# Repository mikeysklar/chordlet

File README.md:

# chordlet
Add a keyboard to your controller.

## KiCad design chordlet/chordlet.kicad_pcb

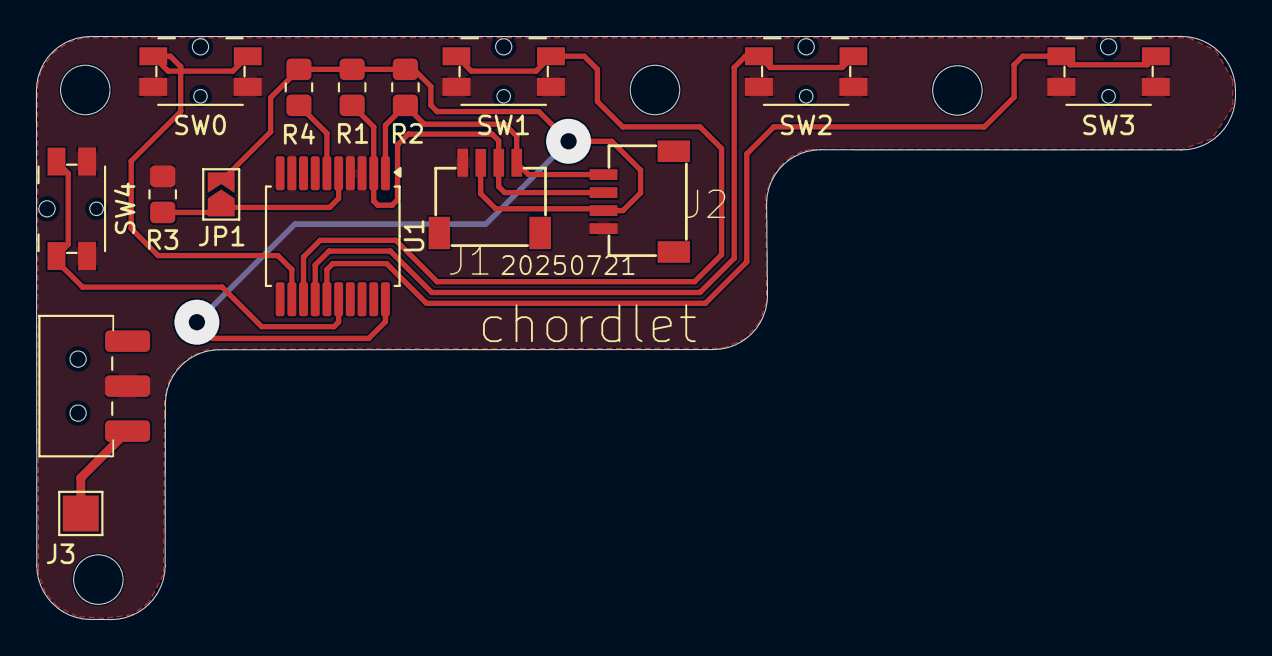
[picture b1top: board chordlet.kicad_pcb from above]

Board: 2 copper layers, 66.6 x 32.4 mm, 15 parts (0 on the bottom side), 12 nets.

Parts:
J1, J2: Conn_01x06_Socket; JST_SH4
J3: Conn_01x01_Pin; TestPoint_Pad_2.0x2.0mm
JP1: SolderJumper_2_Open; SolderJumper-2_P1.3mm_Open_TrianglePad1.0x1.5mm
R1, R2, R3, R4: 10k; R_0805_2012Metric_Pad1.20x1.40mm_HandSolder
SW0, SW1, SW2, SW3, SW4: SW_Push; Panasonic_EVQPUL_EVQPUC
SW5: SW_DPDT_x2; Untitled
U1: MCP23008-xSS; SSOP-20_5.3x7.2mm_P0.65mm

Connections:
/A0: JP1.1 (A), R3.2, U1.5 (A0)
/SCL: J1.4, J2.4, R2.2, U1.1 (SCL)
/SDA: J1.3, J2.3, R1.2, U1.2 (SDA)
/index: SW0.1, U1.12 (GP0)
/middle: SW1.1, U1.13 (GP1)
/pinky: SW3.1, U1.15 (GP3)
/ring: SW2.1, U1.14 (GP2)
/thumb: SW4.1, U1.16 (GP4)
GND: J1.1, J2.1, R3.1, SW0.2, SW1.2, SW2.2, SW3.2, SW4.2, SW5.2 (B), U1.3 (A2), U1.4 (A1), U1.9 (VSS)
unnamed: J3.1, SW5.3 (C)
unnamed: R4.2, U1.6 (~RESET)
VCC: J1.2, J2.2, JP1.2 (B), R1.1, R2.1, R4.1, U1.20 (VDD)

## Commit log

2025-07-18 init
2025-07-19 sch done, pcb layout started
    no errors on import to pcb
2025-07-21 pcb laid out
    looks workable, one vcc jumper needed.
